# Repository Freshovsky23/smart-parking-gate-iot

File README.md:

# Smart Parking Gate System & IoT Data Logger 🚗🅿️🖥️

An automated parking entrance system based on Arduino, integrated with a Python backend and a Dockerized PostgreSQL database for real-time event logging. 

This project demonstrates a complete **IoT pipeline**: from physical hardware sensors and human-machine interaction (HMI), through custom PCB design, up to serial data communication and persistent database storage.

---

## 📺 Project Presentation & Demo

Watch the system in action on YouTube:

> Click the badge above to watch the project implementation and physical mechanical execution details.

---

## 🚀 Key Features

* **Ultrasonic Detection:** Automatically detects arriving vehicles within a range of 2-15 cm using the HC-SR04 sensor.
* **Interactive LCD UI:** A 20x4 character display provides real-time instructions and feedback to the driver.
* **Smooth LED Animations:** Uses PWM (Pulse Width Modulation) for professional-looking fade-in and fade-out effects on status LEDs.
* **Custom PCB Shield:** Features a tailored, 2-layer Arduino Uno Shield designed in KiCad with a solid ground plane (GND copper zone) for stable operation.
* **Smart Event Logging:** Python script (`parking_logger.py`) listens to the Arduino via USB Serial and processes system events in real time.
* **Dockerized Database:** Uses `docker-compose` to instantly spin up a PostgreSQL instance for storing entry/exit logs securely.
* **Debounced Input:** Intelligent button handling with software debouncing and edge detection to prevent accidental double-triggering.

---

## 🛠️ Hardware & PCB Design

The project has evolved from a breadboard prototype into a robust, custom-designed **Arduino Uno Shield** created in KiCad. This ensures optimal signal integrity, eliminates loose jumper wires, and makes the system deployment-ready.

### 📐 PCB View (3D Render)
The board features optimized power traces (0.50 mm), a precise potentiometer for contrast alignment, and a solid ground plane (GND Copper Zone) on the bottom layer.

### 🛠️ Hardware Components
* **Microcontroller:** Arduino Uno R3 (or compatible)
* **Custom PCB:** 2-layer Custom Shield (KiCad design files included)
* **Display:** LCD 20x4 (Hitachi HD44780 compatible)
* **Sensors:** HC-SR04 Ultrasonic Distance Sensor
* **Indications:** * Red LED (Entry blocked)
  * Green LED (Entry allowed)
  * White LED (Object in range)
  * Active/Passive Buzzer (Audio alert)
* **Input:** Tactile Push Button (Gate Close trigger)
* **Passives:** Resistors ($3 \times 220\,\Omega$), Bourns 3386P Potentiometer (LCD Contrast adjust).

---

## 💻 Software Requirements

* **Arduino IDE:** To compile and upload the `.ino` firmware.
* **Docker & Docker Compose:** To containerize and run the PostgreSQL database.
* **Python 3.x:** To execute the serial data logger.
* **Python Libraries:** `pyserial`, `sqlalchemy`, `psycopg2-binary`.

---

## 🔌 Pinout Configuration

| Component | Arduino Pin | Type | Description | Track Width |
| :--- | :---: | :---: | :--- | :---: |
| **VCC (+5V)** | `+5V` | Power | Main power rail for LCD, Sensor, and Potentiometer | **0.50 mm** |
| **GND** | `GND` | Power | Common ground plane (Bottom Copper Zone) | *Copper Zone* |
| **LCD RS** | `D2` | Output | Register Select | 0.25 mm |
| **LCD Enable** | `D3` | Output | Enable Signal | 0.25 mm |
| **LCD D4 - D7** | `D4, D5, D6, D7` | Output | Parallel Data Lines | 0.25 mm |
| **HC-SR04 Trig** | `D8` | Output | Trigger Pulse | 0.25 mm |
| **HC-SR04 Echo** | `D9` | Input | Echo Pulse | 0.25 mm |
| **Red LED** | `D10` | Output (PWM)| Status Indicator (Entry Blocked) | 0.25 mm |
| **Green LED** | `D11` | Output (PWM)| Status Indicator (Entry Allowed) | 0.25 mm |
| **White LED** | `D12` | Output | Range Warning Indicator | 0.25 mm |
| **Push Button** | `D13` | Input | Gate Close Trigger (Internal Pull-up) | 0.25 mm |
| **Buzzer** | `A5 (SCL)` | Output | Audio Alert Signal | 0.25 mm |
| **LCD Contrast**| `RV1 (Pin 2)` | Analog | Contrast adjustment connected to LCD Pin 3 | 0.25 mm |

---

## ⚙️ How to Run the Project (Quick Start)

### 1. Hardware & PCB Setup
1. Open the KiCad files in `hardware/` to inspect the schematic and PCB layout.
2. Fabricate the PCB or assemble the prototype on a breadboard according to the **Pinout Configuration** table.
3. Open `simulator-parking.ino` in the Arduino IDE and upload it to your board.
4. Note the COM port your Arduino is connected to (e.g., `COM9` or `/dev/ttyUSB0`).

### 2. Database Setup (Docker)
1. Open your terminal in the project directory.
2. Start the containerized PostgreSQL database by running:
   ```bash
   docker-compose up -d
3. Backend Data Logger Setup
Navigate to the directory containing parking_logger.py.

Configure your database connection string and correct COM port inside the script.

Run the Python application to start logging events into PostgreSQL:
python parking_logger.py

📂 Repository Structure
Plaintext
├── .github/               # GitHub workflows (if applicable)
├── arduino/               # Arduino firmware (.ino code)
│   └── simulator-parking.ino
├── backend/               # Python application & logger scripts
│   └── parking_logger.py
├── hardware/              # KiCad EDA Project files (Shield Design)
│   ├── Parking.kicad_pro
│   ├── Parking.kicad_sch
│   ├── Parking.kicad_pcb
│   ├── Parking_Schematic.pdf
│   └── Parking.png        # Gorgeous 3D view of the PCB
├── docker-compose.yml     # Docker services initialization (PostgreSQL)
└── README.md              # Documentation
👤 Author
Developer: @Freshovsky23

Contact: Heilman.Wiktor23@gmail.com

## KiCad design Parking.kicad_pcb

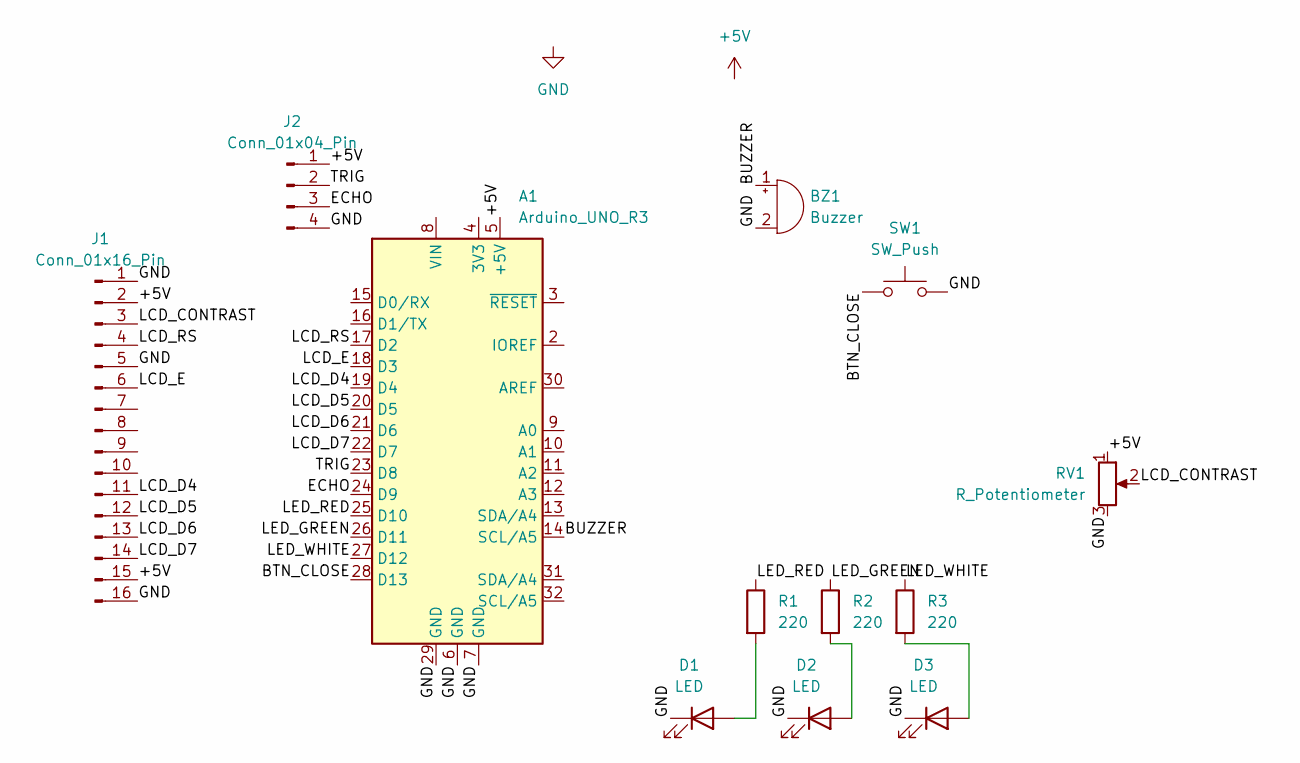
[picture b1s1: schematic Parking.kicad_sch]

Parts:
A1: Arduino_UNO_R3
BZ1: Buzzer; Buzzer_12x9.5RM7.6
D1, D2, D3: LED; LED_D5.0mm
J1: Conn_01x16_Pin; PinHeader_1x16_P2.54mm_Vertical
J2: Conn_01x04_Pin; PinHeader_1x04_P2.54mm_Vertical
R1, R2, R3: 220; R_Axial_DIN0207_L6.3mm_D2.5mm_P7.62mm_Horizontal
RV1: R_Potentiometer; Potentiometer_Bourns_3386P_Vertical
SW1: SW_Push; SW_PUSH_6mm_H5mm

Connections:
+5V: A1.5 (+5V), J1.2, J1.15, J2.1, RV1.1
/BTN_CLOSE: A1.28 (D13), SW1.1
/BUZZER: A1.14 (SCL/A5), BZ1.1 (+)
/ECHO: A1.24 (D9), J2.3
/LCD_CONTRAST: J1.3, RV1.2
/LCD_D4: A1.19 (D4), J1.11
/LCD_D5: A1.20 (D5), J1.12
/LCD_D6: A1.21 (D6), J1.13
/LCD_D7: A1.22 (D7), J1.14
/LCD_E: A1.18 (D3), J1.6
/LCD_RS: A1.17 (D2), J1.4
/LED_GREEN: A1.26 (D11), R2.1
/LED_RED: A1.25 (D10), R1.1
/LED_WHITE: A1.27 (D12), R3.1
/TRIG: A1.23 (D8), J2.2
GND: A1.6 (GND), A1.7 (GND), A1.29 (GND), BZ1.2 (-), D1.1 (K), D2.1 (K), D3.1 (K), J1.1, J1.5, J1.16, J2.4, RV1.3, SW1.2
unnamed: D1.2 (A), R1.2
unnamed: D2.2 (A), R2.2
unnamed: D3.2 (A), R3.2

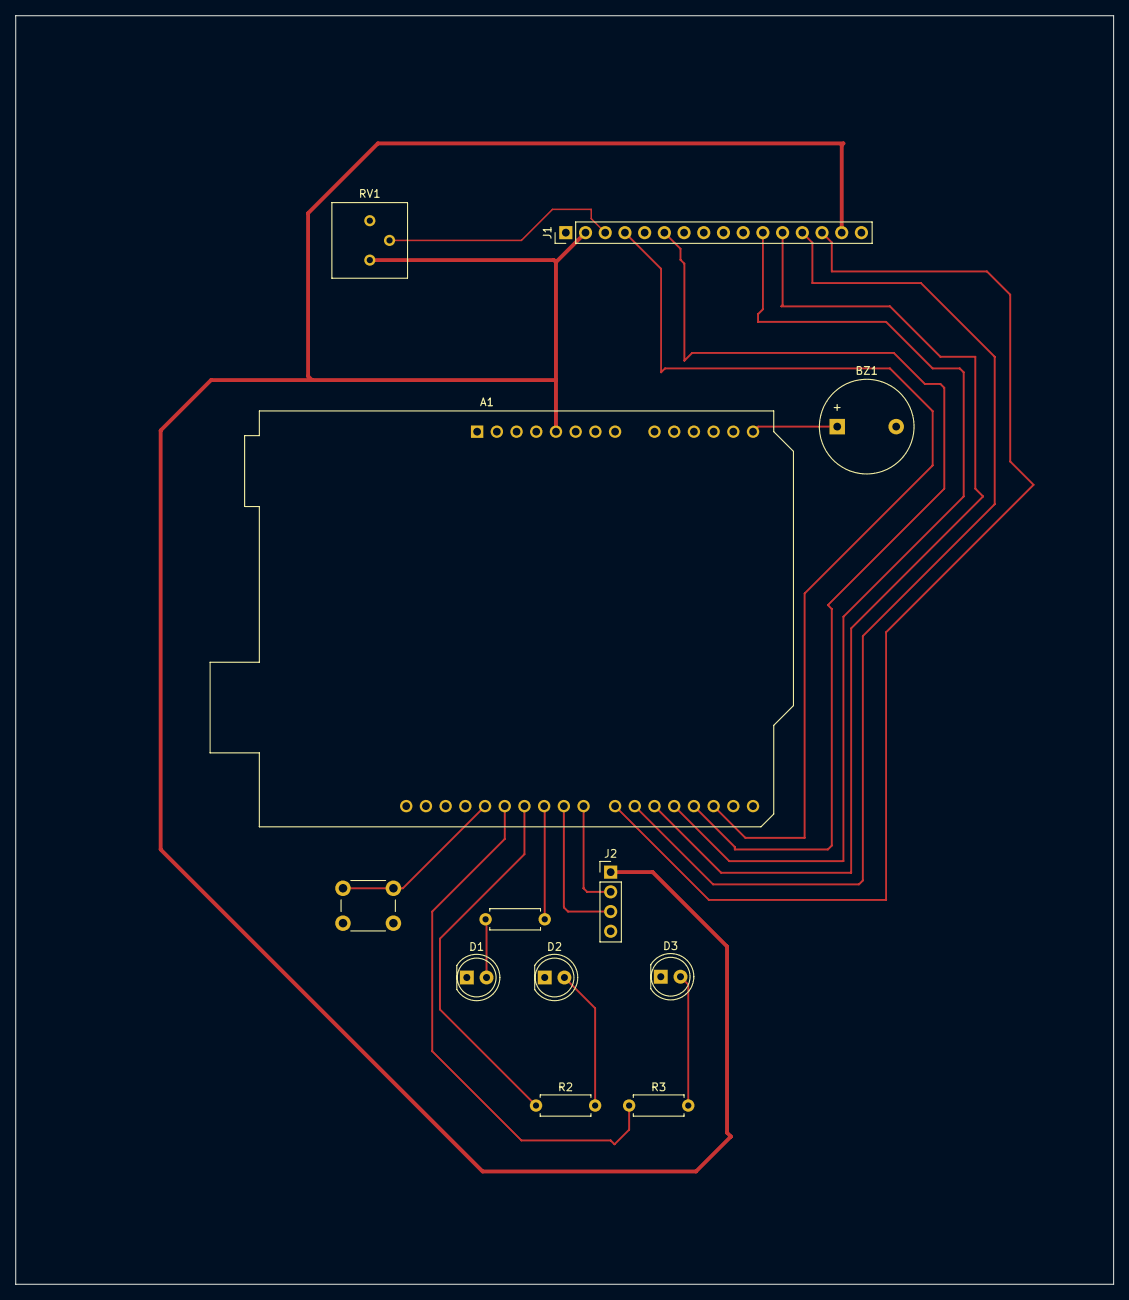
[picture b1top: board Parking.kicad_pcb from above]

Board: 2 copper layers, 141.5 x 163.5 mm, 12 parts (0 on the bottom side), 19 nets.

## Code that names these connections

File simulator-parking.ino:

#include <LiquidCrystal.h> // Include library for LCD display
LiquidCrystal lcd(2, 3, 4, 5, 6, 7); // Create LCD object and assign pins: RS, E, D4, D5, D6, D7

// Pin definitions – using readable names instead of hardcoded numbers
#define echo 9       // Ultrasonic sensor receiver pin (receives the signal)
#define trig 8       // Ultrasonic sensor transmitter pin (sends the signal)
#define buzzer A5    // Buzzer pin
#define greenLED 11  // Green LED pin (PWM) – indicates the gate is open
#define redLED 10    // Red LED pin (PWM) – indicates the gate is closed
#define button 13    // Button pin – the driver presses it after entering the parking lot
#define whiteLED 12  // White LED pin – turns on when a car is in range

// Global variables – storing the state of the program between loop() executions
bool isGateOpen = false;              // Is the gate currently open? At start: no
int currentState = -1;                // Current LCD state: -1=none, 0=welcome, 1=entering
bool previousButtonState = HIGH;      // Previous button reading (HIGH = not pressed, due to INPUT_PULLUP)
bool buttonBeingPressed = false;      // Has the button been registered and not yet released?

void setup() {
  lcd.begin(20, 4);          // Initialize LCD – 20 columns, 4 rows
  Serial.begin(9600);        // Start serial communication (for debugging)
  pinMode(trig, OUTPUT);     // Trig sends the signal – set as output
  pinMode(echo, INPUT);      // Echo receives the signal – set as input
  pinMode(buzzer, OUTPUT);   // Buzzer plays sound – set as output
  pinMode(greenLED, OUTPUT); // Green LED – set as output
  pinMode(redLED, OUTPUT);   // Red LED – set as output
  pinMode(whiteLED, OUTPUT); // White LED – set as output
  pinMode(button, INPUT_PULLUP); // Button as input with an internal pull-up resistor
                                 // INPUT_PULLUP means: not pressed = HIGH, pressed = LOW

  analogWrite(redLED, 255); // At startup, turn the red LED on fully – gate is closed
}

void loop()
{
  checkRange(2, 15);  // Check if a car is within 2-15 cm from the sensor
  checkButton();      // Check if the driver pressed the button after entering
}

void showWelcomeScreen()
// Displays the welcome screen when no one is at the gate
{
  lcd.clear();                        // Clear the entire LCD screen
  lcd.setCursor(0, 0);                // Set cursor to: column 0, row 0
  lcd.print("Welcome to parking");    // Display text in row 0
  lcd.setCursor(0, 1);                // Move to row 1
  lcd.print("Heilman industries");    // Display text in row 1
  lcd.setCursor(0, 2);                // Move to row 2
  lcd.print("Waiting for");           // Display text in row 2
  lcd.setCursor(0, 3);                // Move to row 3
  lcd.print("a vehicle");             // Display text in row 3
  lcd.blink();                        // Turn on the blinking cursor on the LCD

  digitalWrite(whiteLED, LOW); // Turn off the white LED – no one is there
  digitalWrite(buzzer, LOW);   // Ensure the buzzer is off
}

long measureDistance()
// Measures the distance in centimeters using the HC-SR04 ultrasonic sensor
// Principle of operation: send a short pulse, measure how long the echo takes to return
{
  long duration;
  digitalWrite(trig, LOW);        // Ensure trig is off before measuring
  delayMicroseconds(2);           // Wait 2 microseconds for stability
  digitalWrite(trig, HIGH);       // Send ultrasonic pulse
  delayMicroseconds(10);          // The pulse must last exactly 10 microseconds
  digitalWrite(trig, LOW);        // End the pulse

  duration = pulseIn(echo, HIGH); // Measure the time (in microseconds) for the echo to return
  delay(100);                     // Short pause before the next measurement
  return (duration / 58);         // Convert time to centimeters (speed of sound: ~340m/s, round trip)
}

void checkRange(int a, int b)
// Checks if the measured distance falls within the range (a, b) centimeters
// If yes and the gate is closed – opens the gate and lets the car in
{
  long distance = measureDistance(); // Get current distance from the sensor

  if (distance > a && distance < b && isGateOpen == false)
  // Condition: car is close (2-15 cm) AND the gate is still closed
  {
    lcd.clear();
    lcd.setCursor(0, 0);
    lcd.print("Please enter"); // Inform the driver they can enter
    
    // Request for double click split into two rows (fits exactly 20 chars)
    lcd.setCursor(0, 1);
    lcd.print("After entering press");
    lcd.setCursor(0, 2);
    lcd.print("the button 2 times");
    
    lcd.blink();                  // Turn on the blinking cursor

    digitalWrite(whiteLED, HIGH); // Turn on the white LED – car detected

    turnOffLED(redLED);           // Smoothly fade out the red LED (animation)
    turnOnLED(greenLED);          // Smoothly fade in the green LED (animation)

    digitalWrite(buzzer, HIGH);   // Play a beep for 1 second
    delay(1000);
    digitalWrite(buzzer, LOW);    // Turn off the buzzer

    isGateOpen = true; // Remember that the gate is now open
    currentState = 1;  // Set state: car is entering
    Serial.println("GATE_OPENED");
  }
  else if (isGateOpen == false && currentState != 0)
  // Condition: gate is closed AND the screen is not yet showing the welcome message
  // (currentState != 0 prevents continuous refreshing of the welcome screen)
  {
    showWelcomeScreen(); // Display the welcome screen
    currentState = 0;    // Remember that we are showing the welcome screen
  }
}

void checkButton()
// Handles the button that the driver presses after entering the parking lot
// Uses falling edge detection – responds only at the MOMENT of a press,
// not just the fact that the button is held down
{
  bool currentButtonState = digitalRead(button); // Read the current state of the button

  // If the button was released – remove the lock
  // This allows the next press to be detected as a new event
  if (currentButtonState == HIGH)
  {
    buttonBeingPressed = false; // Reset flag – button is free to be used again
  }

  // Detect falling edge: previously HIGH (released), now LOW (pressed)
  // We also check the flag – was this press already handled?
  bool justPressed = false;
  if (previousButtonState == HIGH && currentButtonState == LOW && !buttonBeingPressed)
  {
    delay(50); // Debouncing: wait 50ms for the mechanical contacts to stabilize
               // (mechanical buttons "bounce" for a fraction of a second when pressed)
    if (digitalRead(button) == LOW) // Confirm it's a real press, not a bounce
    {
      justPressed = true;           // Yes – button genuinely pressed
      buttonBeingPressed = true;    // Block further detections until the button is released
    }
  }

  if (isGateOpen == true && justPressed)
  // Close the gate only if: gate is open AND button was just pressed
  {
    lcd.clear();
    lcd.setCursor(0, 0);
    lcd.print("Closing the gate..."); // Inform about closing
    lcd.blink();                      // Turn on the blinking cursor
    delay(1500);                      // Wait 1.5 seconds (time for the gate to close)

    digitalWrite(whiteLED, LOW); // Turn off the white LED – car has entered

    turnOffLED(greenLED);        // Smoothly fade out the green LED (animation)
    turnOnLED(redLED);           // Smoothly fade in the red LED (animation)

    isGateOpen = false; // Remember that the gate is closed
    currentState = -1;  // Reset state – loop() will return to the welcome screen shortly
    Serial.println("GATE_CLOSED");
  }

  previousButtonState = currentButtonState; // Remember the state for the next loop() iteration
}

void turnOnLED(int color)
// Smoothly brightens the LED passed as an argument (uses PWM)
// The entire fade-in takes about 1.3 seconds (256 steps x 5ms)
{
  for (int i = 0; i <= 255; i++) // From 0 (off) to 255 (full brightness)
  {
    analogWrite(color, i); // Set LED brightness to value i (0-255)
    delay(5);              // Wait 5ms before the next step
  }
}

void turnOffLED(int color)
// Smoothly dims the LED passed as an argument (uses PWM)
// The entire fade-out takes about 1.3 seconds (256 steps x 5ms)
{
  for (int i = 255; i >= 0; i--) // From 255 (full brightness) down to 0 (off)
  {
    analogWrite(color, i); // Set LED brightness to value i (0-255)
    delay(5);              // Wait 5ms before the next step
  }
}

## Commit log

2026-05-11 adding movie
2026-06-06 Enhance README with project demo and presentation
    Added project presentation section with YouTube demo link.
2026-06-06 Update README with game instructions and author info
    Added instructions for resetting the game and winning conditions, along with software libraries used and author information.
2026-06-06 Update README to simplify database setup instructions
    Removed unnecessary details about game rules and author information from the README.
2026-06-07 feat: integrate custom KiCad PCB shield hardware design and update documentation
2026-06-07 Fix image path in README for PCB render
2026-06-07 Update image path for PCB 3D render in README
2026-06-07 feat: add custom KiCad PCB shield design and update README
